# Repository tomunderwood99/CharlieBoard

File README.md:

# The CharlieBoard

An open-source LED display system for the MBTA that runs on Raspberry Pi Zero 2W with WS2812B LEDs. Features real-time transit data visualization, web control interface, and geographically accurate station mapping. PCBs for the Red, Orange, and Blue line are live! Green line in progress :)

## Quick Start

**Prerequisites:** 
- Raspberry Pi Zero 2W with Debian Trixie 64-bit Lite
- WS2812B LED strip or custom PCB
- WiFi (configured during pi setup)
- SSH enabled (RPI Connect recommended)
- [MBTA API key](https://api-v3.mbta.com/)

For hardware assembly instructions, see the [Hardware Assembly Guide](docs/hardware_assembly_guide.md).

Run the following commands to install and initialize the display.

```bash
sudo apt update && sudo apt install -y git python3-pip

cd ~
git clone --filter=blob:none --sparse https://github.com/tomunderwood99/CharlieBoard.git

cd CharlieBoard
git sparse-checkout set --no-cone '/*' '!hardware'

chmod +x deployment/quick_start/setup_mbta_controller.sh

# Optional: use flags to set custom recovery wifi settings:
# --with-wifi-helper
# --ap-ssid "CustomWifiName"
# --ap-password "YourStrongPassword"

sudo ./deployment/quick_start/setup_mbta_controller.sh
```

The setup script will prompt for your MBTA API key and various setting inputs. After completion, access the web interface at `http://your-hostname.local:8000` on your local network. Settings can be changed from the web interface or from the command line using the `charlieboard` command. See the [CLI reference](docs/cli.md) for details.

**Optional enhancement:** Set up a reverse proxy to access the web interface at `http://hostname.local` without the port number. See the [nginx reverse proxy setup guide](docs/nginx_reverse_proxy_setup.md).

**Note:** The sparse-checkout excludes the `hardware/` directory (PCB design files) to speed up cloning. This setting persists across future `git pull` operations. If you need the hardware files, run: `git sparse-checkout disable`

## Features

- **Real-time Transit Data**: Live vehicle positions, occupancy, and speed data
- **Geographically Accurate**: Stations are marked on a real map
- **Web Control Interface**: Remote control from any device on your network
- **Customizable Display**: Adjustable brightness, colors, and display hours
- **Reliable Operation**: Automatic recovery, health monitoring, and maintenance

## Hardware

| Component | Notes |
|-----------|-------|
| Raspberry Pi Zero 2W | Main controller |
| WS2812B LEDs | Custom PCB (\~\$120 for 5) or LED strips (\~\$20) |
| 5V 4A Power Supply | Powers Pi and LEDs |
| MicroSD Card (16GB+) | For OS and software |
| Display Enclosure | Picture frame or custom case |

**Total Cost**: $50–180 depending on LED choice

Complete PCB design files (Gerber + KiCad) are available in `hardware/PCB Production/`. See the [Bill of Materials](docs/bill_of_materials.md) for detailed pricing and sourcing.

## Documentation

| Guide | Description |
|-------|-------------|
| [Quick Start Guide](deployment/quick_start/QUICK_START_GUIDE.md) | Step-by-step setup walkthrough |
| [Terminal CLI](docs/cli.md) | Change settings from SSH without the web UI |
| [Complete Setup Guide](docs/complete_setup_guide.md) | Detailed manual configuration |
| [Bill of Materials](docs/bill_of_materials.md) | Hardware pricing and sourcing |
| [Hardware Assembly](docs/hardware_assembly_guide.md) | PCB assembly instructions |
| [Operations & Troubleshooting](docs/operations_and_troubleshooting.md) | Maintenance and problem solving |
| [Transit System Adaptation](docs/transit_system_adaptation_guide.md) | Adapt for other transit systems |
| [Map Making with QGIS](docs/map_making_with_qgis.md) | Create custom transit maps ([example project](https://drive.google.com/drive/folders/1vFNIh-ThJNZXUUT2JSJMrOyUVWq9bhA2?usp=drive_link)) |

## Contributing

Contributions are welcome! Please:

1. Fork the repository
2. Create a feature branch (`git checkout -b feature/amazing-feature`)
3. Test on Raspberry Pi Zero 2W hardware
4. Commit your changes (`git commit -m 'Add amazing feature'`)
5. Push and open a Pull Request

Follow existing code style, update documentation for new features, and add comments for complex logic. Contributions to **software** are under the MIT License; contributions to **`hardware/`** design files are under CERN-OHL-S, as described in [License](#license).

## License

This repository uses two licenses:

| Scope | License | Full text |
|-------|---------|-----------|
| **Software** (Python, scripts, configs, docs outside `hardware/`, and everything except the `hardware/` tree) | [MIT License](https://opensource.org/licenses/MIT) | [LICENSE](LICENSE) |
| **`hardware/`** (PCB designs, KiCad projects, Gerbers, and related production files in this directory) | [CERN Open Hardware Licence v2 — Strongly Reciprocal (CERN-OHL-S)](https://ohwr.org/project/cernohl/wikis/Documents/CERN-OHL-version-2) | [LICENSE-CERN-OHL-S](LICENSE-CERN-OHL-S) |

Third-party materials bundled under `hardware/` may carry their own licenses (see notices in those subfolders).

Copyright © 2025 Thomas Underwood

<details>
<summary>Disclaimers & Attributions</summary>

### AI Assistance
This project was developed with the assistance of AI coding tools. All code has been reviewed, tested, and validated on actual hardware.

### Data Sources
This project uses data from:
- **MBTA and MassDOT** – Transit data via [MBTA V3 API](https://api-v3.mbta.com/)
- **MassGIS** – Geographic and mapping data

All data is provided "as is" without warranties. This project is not affiliated with, endorsed by, or sponsored by MBTA, MassDOT, MassGIS, or the Commonwealth of Massachusetts.
</details>

## Support

- Check the [Operations and Troubleshooting Guide](docs/operations_and_troubleshooting.md)
- Review logs: `sudo journalctl -u mbta_display -n 100`
- Open an issue on GitHub with your Pi model, OS version, and error details
- [MBTA V3 API Documentation](https://api-v3.mbta.com/) · [Raspberry Pi GPIO Pinout](https://pinout.xyz/) · [Adafruit NeoPixel Guide](https://learn.adafruit.com/adafruit-neopixel-uberguide)

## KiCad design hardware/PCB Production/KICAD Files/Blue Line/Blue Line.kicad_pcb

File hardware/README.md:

# Hardware

Design files in this directory (KiCad projects, Gerbers, BOM-related assets, and other PCB production materials) are licensed under **CERN Open Hardware Licence Version 2 — Strongly Reciprocal (CERN-OHL-S)**.

The complete license text is in the repository root: [LICENSE-CERN-OHL-S](../LICENSE-CERN-OHL-S). The rest of the CharlieBoard repository (software, deployment scripts, and documentation outside `hardware/`) is under the MIT License: [LICENSE](../LICENSE).

Some subfolders include third-party symbols or footprints with their own license files—check those folders for additional terms.

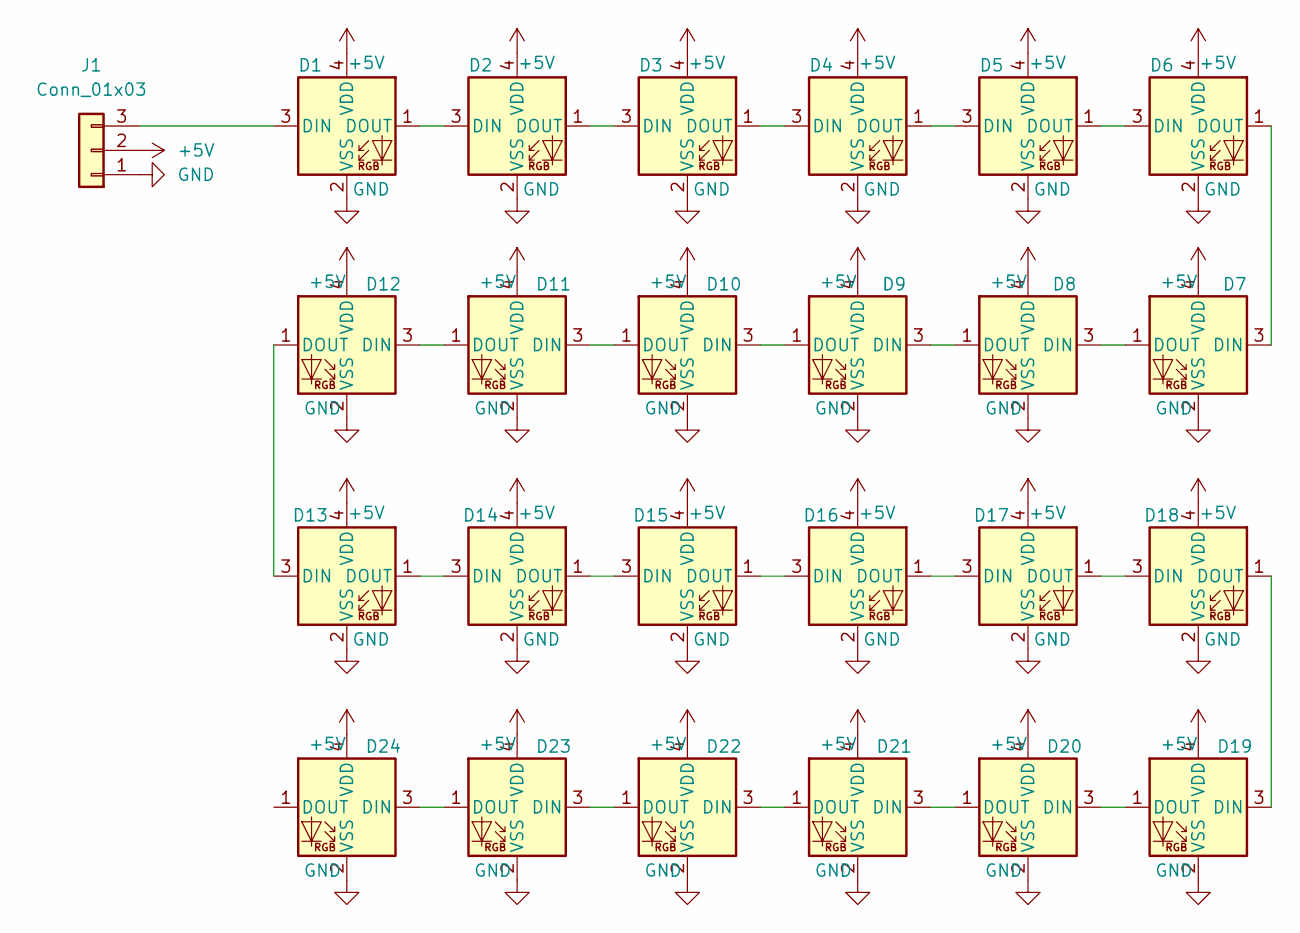
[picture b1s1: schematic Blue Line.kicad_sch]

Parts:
D1, D2, D3, D4, D5, D6, D7, D8, D9, D10, D11, D12, D13, D14, D15, D16, D17, D18, D19, D20, D21, D22, D23, D24: WS2812B-2020; LED_WS2812B-2020_PLCC4_2.0x2.0mm; LCSC C965555
J1: Conn_01x03; CONN3_S3B-PH_JST

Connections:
+5V: D1.4 (VDD), D2.4 (VDD), D3.4 (VDD), D4.4 (VDD), D5.4 (VDD), D6.4 (VDD), D7.4 (VDD), D8.4 (VDD), D9.4 (VDD), D10.4 (VDD), D11.4 (VDD), D12.4 (VDD), D13.4 (VDD), D14.4 (VDD), D15.4 (VDD), D16.4 (VDD), D17.4 (VDD), D18.4 (VDD), D19.4 (VDD), D20.4 (VDD), D21.4 (VDD), D22.4 (VDD), D23.4 (VDD), D24.4 (VDD), J1.2
GND: D1.2 (VSS), D2.2 (VSS), D3.2 (VSS), D4.2 (VSS), D5.2 (VSS), D6.2 (VSS), D7.2 (VSS), D8.2 (VSS), D9.2 (VSS), D10.2 (VSS), D11.2 (VSS), D12.2 (VSS), D13.2 (VSS), D14.2 (VSS), D15.2 (VSS), D16.2 (VSS), D17.2 (VSS), D18.2 (VSS), D19.2 (VSS), D20.2 (VSS), D21.2 (VSS), D22.2 (VSS), D23.2 (VSS), D24.2 (VSS), J1.1
unnamed: D1.3 (DIN), J1.3
unnamed: D1.1 (DOUT), D2.3 (DIN)
unnamed: D2.1 (DOUT), D3.3 (DIN)
unnamed: D3.1 (DOUT), D4.3 (DIN)
unnamed: D4.1 (DOUT), D5.3 (DIN)
unnamed: D5.1 (DOUT), D6.3 (DIN)
unnamed: D6.1 (DOUT), D7.3 (DIN)
unnamed: D7.1 (DOUT), D8.3 (DIN)
unnamed: D8.1 (DOUT), D9.3 (DIN)
unnamed: D9.1 (DOUT), D10.3 (DIN)
unnamed: D10.1 (DOUT), D11.3 (DIN)
unnamed: D11.1 (DOUT), D12.3 (DIN)
unnamed: D12.1 (DOUT), D13.3 (DIN)
unnamed: D13.1 (DOUT), D14.3 (DIN)
unnamed: D14.1 (DOUT), D15.3 (DIN)
unnamed: D15.1 (DOUT), D16.3 (DIN)
unnamed: D16.1 (DOUT), D17.3 (DIN)
unnamed: D17.1 (DOUT), D18.3 (DIN)
unnamed: D18.1 (DOUT), D19.3 (DIN)
unnamed: D19.1 (DOUT), D20.3 (DIN)
unnamed: D20.1 (DOUT), D21.3 (DIN)
unnamed: D21.1 (DOUT), D22.3 (DIN)
unnamed: D22.1 (DOUT), D23.3 (DIN)
unnamed: D23.1 (DOUT), D24.3 (DIN)

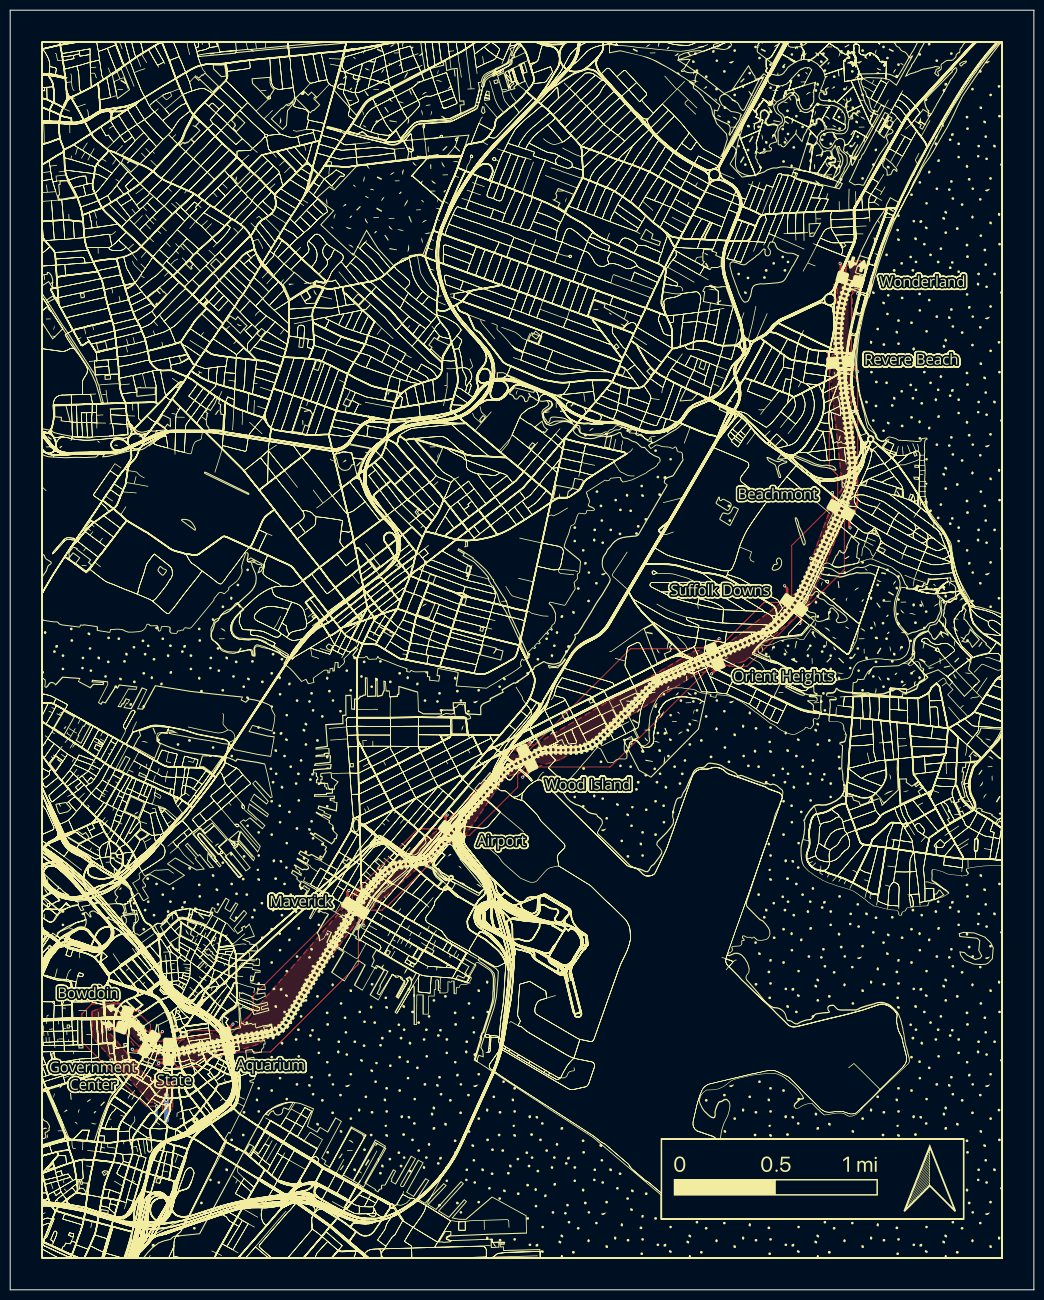
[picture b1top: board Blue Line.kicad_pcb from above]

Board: 2 copper layers, 203.2 x 254.0 mm, 25 parts (1 on the bottom side), 26 nets.

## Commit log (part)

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2026-01-29 launch code! v1.0 :)
2026-01-30 updating readme / docs
2026-01-30 formatting - remove lines!
2026-01-30 added wiring image (fritzing)
2026-01-30 added gqis map to google drive
2026-01-31 final
2026-02-01 corrected gerber files- still need to correct KiCAD
2026-02-01 kicad files are/were correct
2026-02-01 updating POS for new kicad/gerber
2026-02-01 cleaning up kicad stuff
2026-04-03 updating license and install guides (wrong directory)
2026-05-06 adding headless wifi helper, blue/orange production files, and reorg
    1) Added headless_wifi_helper, making it easier to send pre-flashed boards or move them between locations
    2) Converted all logic to use nmcli as this is the more modern approach
    3) Added orange and blue line production files (they've been ordered! Have yet to receive and test them)
    4) Did some reorganization of production files, gitignore etc
2026-05-06 Remove ignored files from repository
2026-06-09 updating station_led_maps and blue line production files
    Turns out ground planes are important ;) I definitely didn't forget to add one in the blue line PCB
2026-06-09 Add charlieboard CLI, brightness multiplier, and corrected LED maps. Port terminal settings tooling from private development and fix Blue/Orange station LED direction mappings.
2026-06-10 modifying cli responses and adding brightness cli

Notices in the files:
README.md:
Hardware: CERN-OHL-S
